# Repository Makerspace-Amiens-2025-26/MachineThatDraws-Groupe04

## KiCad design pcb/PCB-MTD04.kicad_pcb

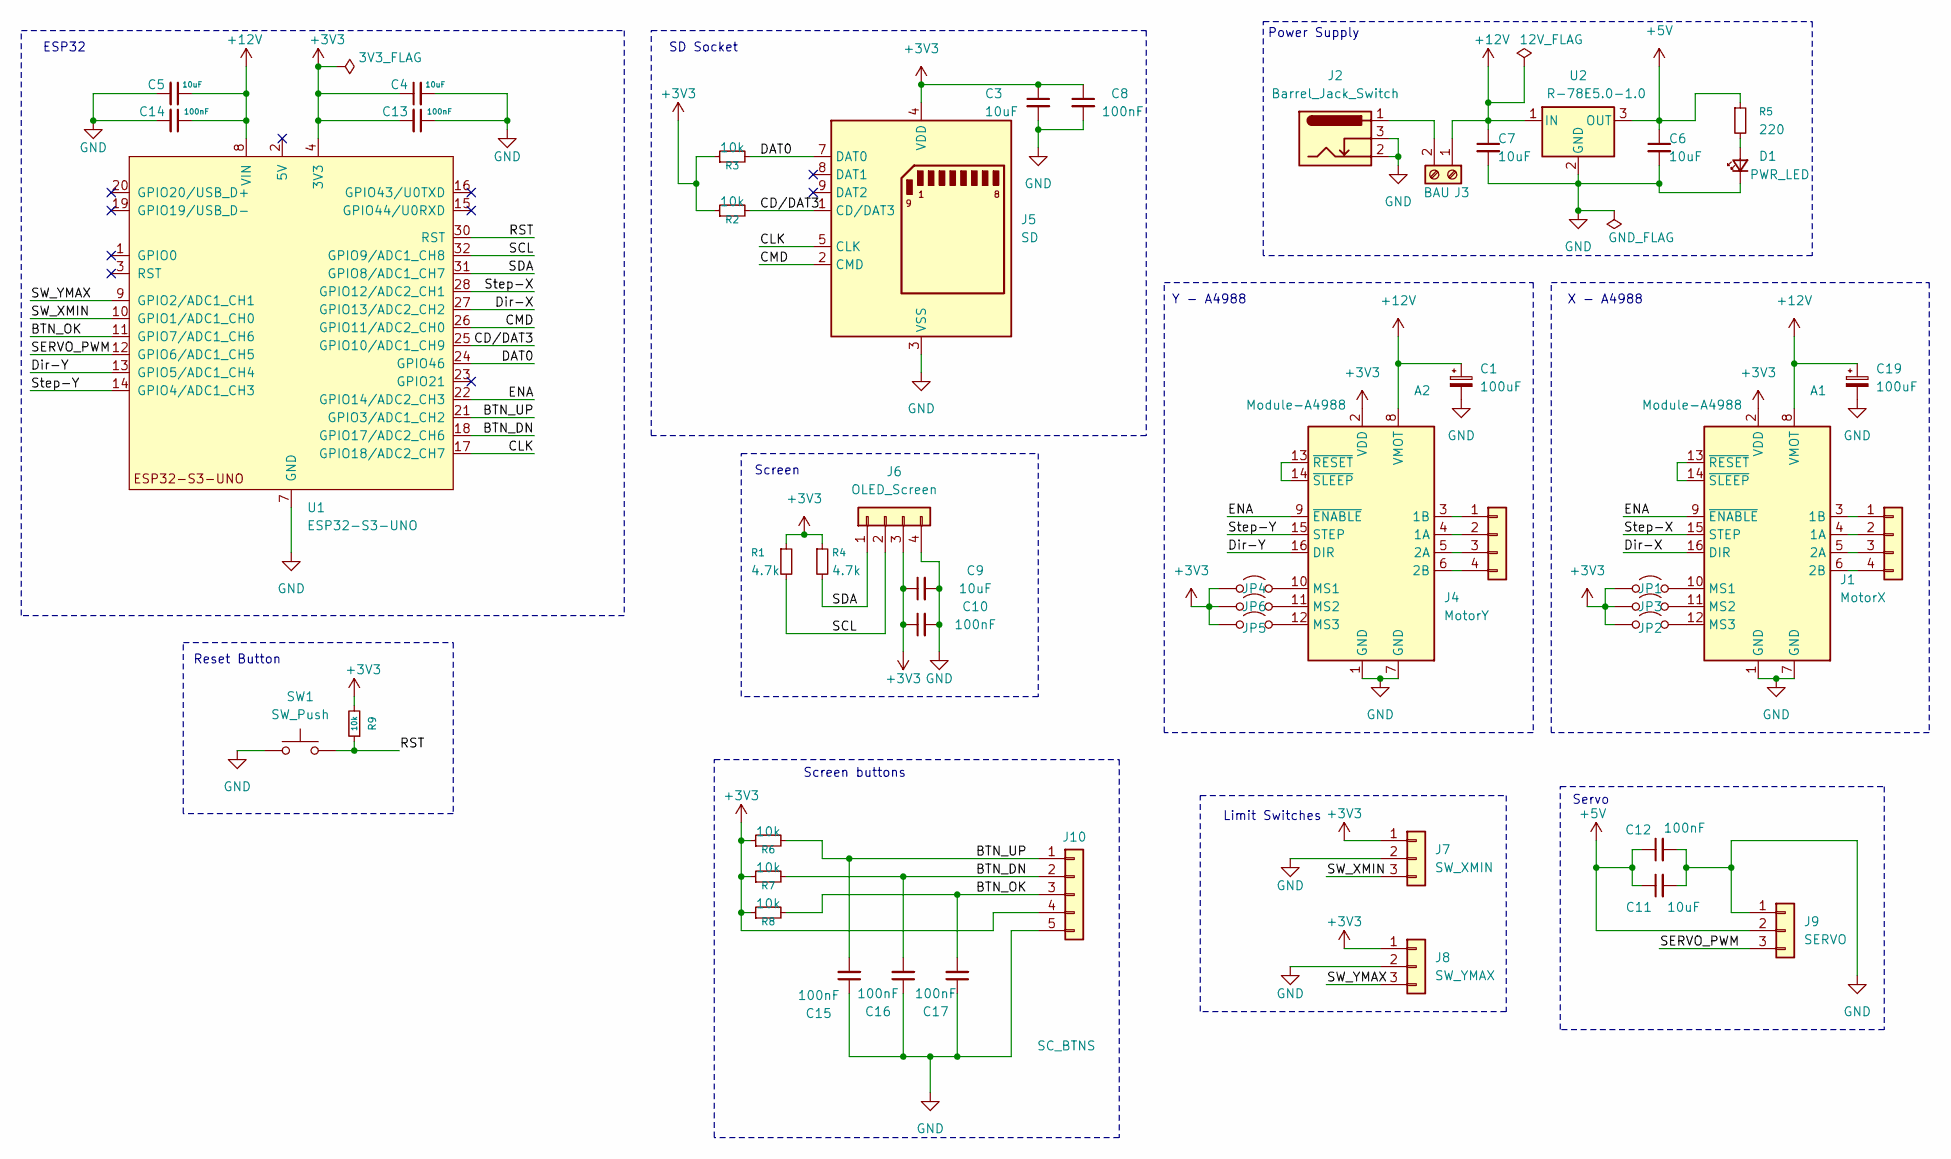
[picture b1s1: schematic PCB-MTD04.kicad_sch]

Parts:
A1, A2: Module-A4988; Pololu_Breakout-16_15.2x20.3mm
C1, C19: 100uF; CP_Radial_D8.0mm_P3.50mm
C3, C4, C5, C6, C7, C9, C11: 10uF; C_1206
C8, C10, C12, C13, C14, C15, C16, C17: 100nF; C_1206
D1: PWR_LED; LED_1206_3216Metric_Pad1.42x1.75mm_HandSolder
J1: MotorX; PinHeader_1x04_P2.54mm_Vertical
J2: Barrel_Jack_Switch; BarrelJack_Horizontal
J3: BAU; TerminalBlock_MaiXu_MX126-5.0-02P_1x02_P5.00mm
J4: MotorY; PinHeader_1x04_P2.54mm_Vertical
J5: SD; SD_Hirose_DM1AA_SF_PEJ82
J6: OLED_Screen; PinHeader_1x04_P2.54mm_Vertical
J7: SW_XMIN; PinHeader_1x03_P2.54mm_Vertical
J8: SW_YMAX; PinHeader_1x03_P2.54mm_Vertical
J9: SERVO; PinHeader_1x03_P2.54mm_Vertical
J10: SC_BTNS; PinHeader_1x05_P2.54mm_Vertical
JP1, JP2, JP3, JP4, JP5, JP6: Jumper_2_Open; PinHeader_1x02_P2.54mm_Vertical
R1, R4: 4.7k; R_1206
R2, R3, R6, R7, R8, R9: 10k; R_1206
R5: 220; R_1206
SW1: SW_Push; SW_Push_KMR2
U1: ESP32-S3-UNO; ESP_S3_UNO
U2: R-78E5.0-1.0; Converter_DCDC_RECOM_R-78E-0.5_THT

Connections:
+3V3: A1.2 (VDD), A2.2 (VDD), C3.1, C4.1, C8.1, C9.1, C10.1, C13.2, J5.4 (VDD), J6.3, J7.1, J8.1, J10.4, JP1.1 (A), JP2.1 (A), JP3.1 (A), JP4.1 (A), JP5.1 (A), JP6.1 (A), R1.1, R2.1, R3.1, R4.1, R6.1, R7.1, R8.1, R9.2, U1.4 (3V3)
+5V: C6.1, C11.1, C12.1, J9.2, R5.1, U2.3 (OUT)
+12V: A1.8 (VMOT), A2.8 (VMOT), C1.1, C5.1, C7.1, C14.1, C19.1, J3.1, U1.8 (VIN), U2.1 (IN)
/BTN_DN: C16.2, J10.2, R7.2, U1.18 (GPIO17/ADC2_CH6)
/BTN_OK: C17.2, J10.3, R8.2, U1.11 (GPIO7/ADC1_CH6)
/BTN_UP: C15.2, J10.1, R6.2, U1.21 (GPIO3/ADC1_CH2)
/CD/DAT3: J5.1 (CD/DAT3), R2.2, U1.25 (GPIO10/ADC1_CH9)
/CLK: J5.5 (CLK), U1.17 (GPIO18/ADC2_CH7)
/CMD: J5.2 (CMD), U1.26 (GPIO11/ADC2_CH0)
/DAT0: J5.7 (DAT0), R3.2, U1.24 (GPIO46)
/Dir-X: A1.16 (DIR), U1.27 (GPIO13/ADC2_CH2)
/Dir-Y: A2.16 (DIR), U1.13 (GPIO5/ADC1_CH4)
/ENA: A1.9 (~ENABLE), A2.9 (~ENABLE), U1.22 (GPIO14/ADC2_CH3)
/RST: R9.1, SW1.2, U1.30 (RST)
/SCL: J6.2, R1.2, U1.32 (GPIO9/ADC1_CH8)
/SDA: J6.1, R4.2, U1.31 (GPIO8/ADC1_CH7)
/SERVO_PWM: J9.3, U1.12 (GPIO6/ADC1_CH5)
/SW_XMIN: J7.3, U1.10 (GPIO1/ADC1_CH0)
/SW_YMAX: J8.3, U1.9 (GPIO2/ADC1_CH1)
/Step-X: A1.15 (STEP), U1.28 (GPIO12/ADC2_CH1)
/Step-Y: A2.15 (STEP), U1.14 (GPIO4/ADC1_CH3)
GND: A1.1 (GND), A1.7 (GND), A2.1 (GND), A2.7 (GND), C1.2, C3.2, C4.2, C5.2, C6.2, C7.2, C8.2, C9.2, C10.2, C11.2, C12.2, C13.1, C14.2, C15.1, C16.1, C17.1, C19.2, D1.1 (K), J2.2, J2.3, J5.3 (VSS), J5.6 (VSS), J6.4, J7.2, J8.2, J9.1, J10.5, SW1.1, U1.6 (GND), U1.7 (GND), U1.29 (GND), U2.2 (GND)
unnamed: A1.4 (1A), J1.2
unnamed: A1.3 (1B), J1.1
unnamed: A1.5 (2A), J1.3
unnamed: A1.6 (2B), J1.4
unnamed: A1.10 (MS1), JP1.2 (B)
unnamed: A1.11 (MS2), JP2.2 (B)
unnamed: A1.12 (MS3), JP3.2 (B)
unnamed: A1.13 (~RESET), A1.14 (~SLEEP)
unnamed: A2.4 (1A), J4.2
unnamed: A2.3 (1B), J4.1
unnamed: A2.5 (2A), J4.3
unnamed: A2.6 (2B), J4.4
unnamed: A2.10 (MS1), JP4.2 (B)
unnamed: A2.11 (MS2), JP5.2 (B)
unnamed: A2.12 (MS3), JP6.2 (B)
unnamed: A2.13 (~RESET), A2.14 (~SLEEP)
unnamed: D1.2 (A), R5.2
unnamed: J2.1, J3.2

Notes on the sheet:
ESP32
Screen buttons
Limit Switches
Screen
X - A4988
Reset Button
Servo
SD Socket
Y - A4988
Power Supply

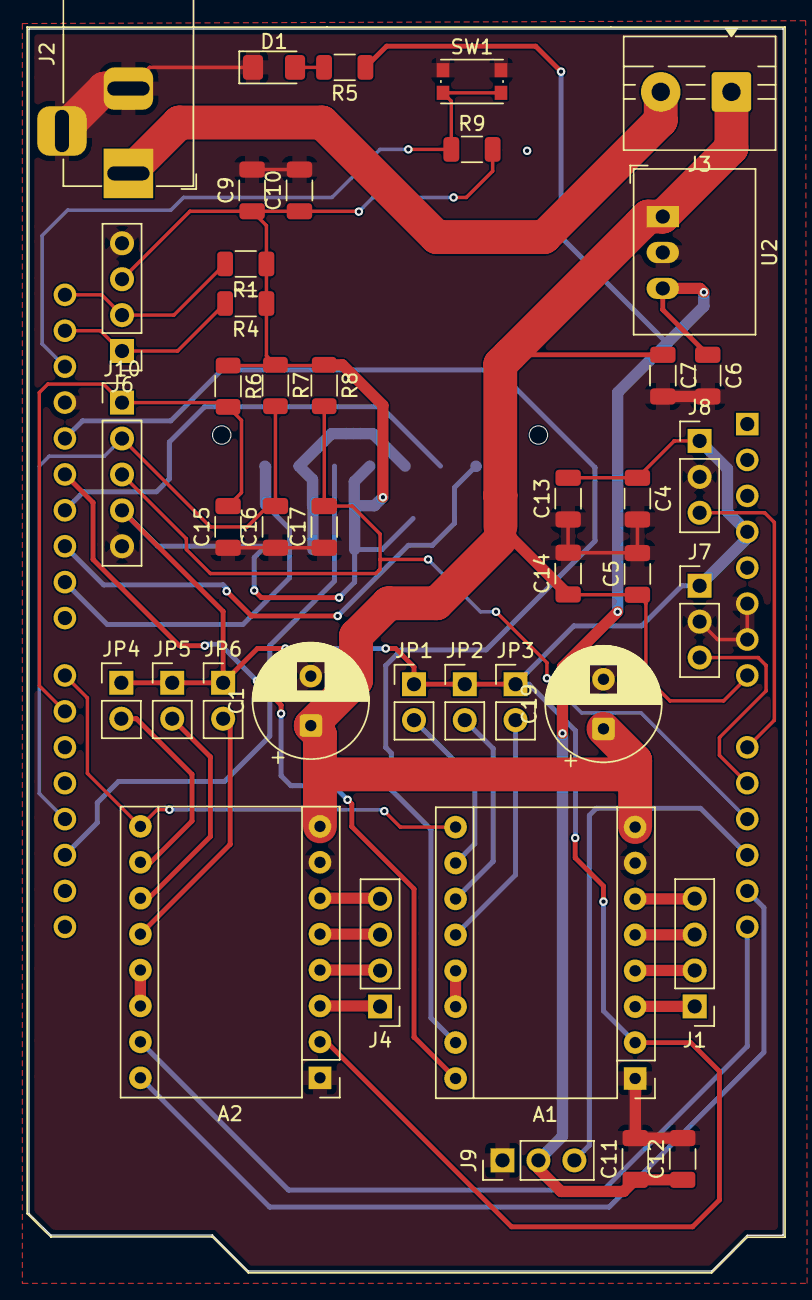
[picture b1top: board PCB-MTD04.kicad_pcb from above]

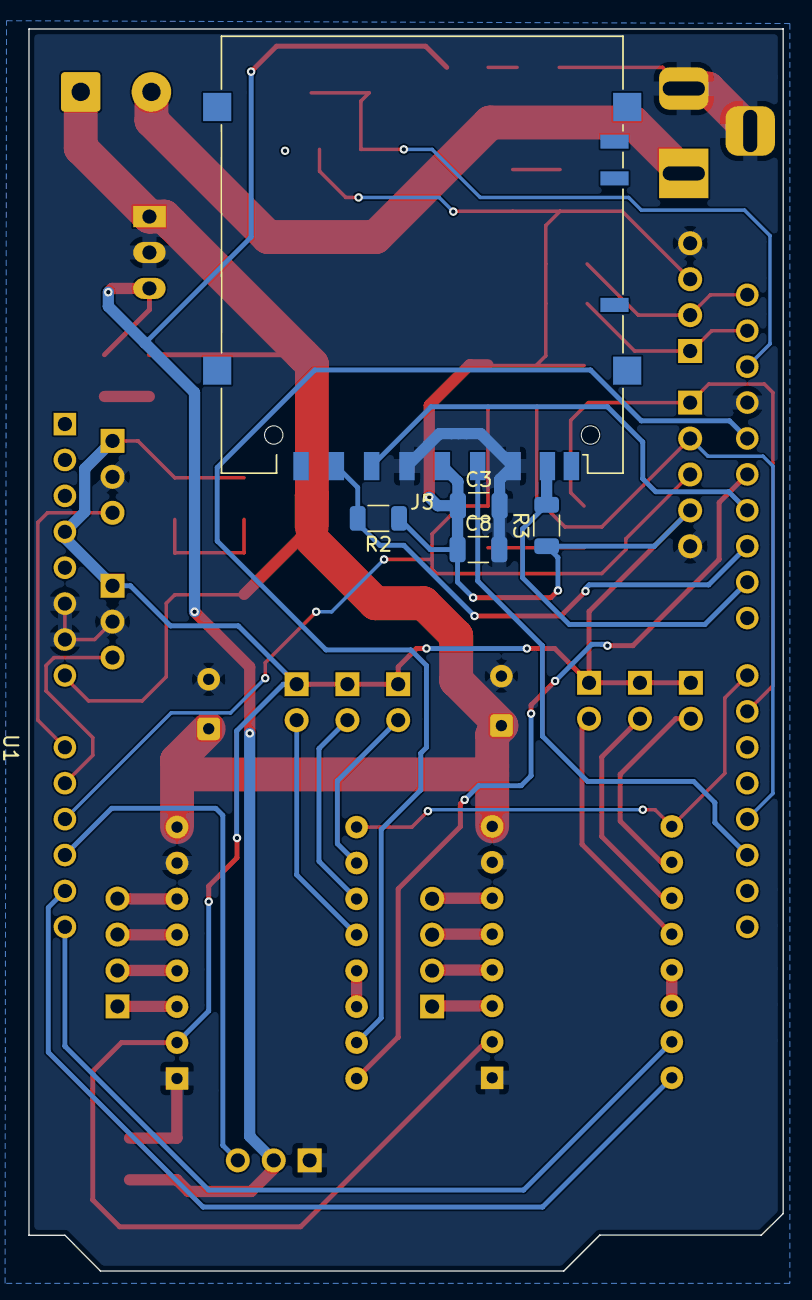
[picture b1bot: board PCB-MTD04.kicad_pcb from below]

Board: 2 copper layers, 53.3 x 87.8 mm, 48 parts (5 on the bottom side), 40 nets.

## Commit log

2026-03-11 Fichier Carte
2026-03-11 Create Test
2026-04-10 Create docs
2026-04-10 Restart action
2026-04-10 update to custom static site action
2026-04-10 essai client
2026-04-10 changed "assets" folder
2026-04-10 add pictures
2026-04-10 ajout img3
2026-04-10 change
2026-04-10 Rename docs/fichiers_kicad/.glb to docs/fichiers_kicad/src="fichiers_kicad/kicad.glb
2026-04-10 Rename kicad.glb to pcb.glb
2026-04-22 mise en route de rendu
2026-04-24 uploadPCB
2026-04-24 Validation PCB pour production
    Attention :
    - plan de masse "Front et Bottom"
    - Possible collision entre lecteur SD et Barrel Jack Uno
